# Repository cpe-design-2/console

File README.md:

# `goco`

An open-source video game console for games built using the [Godot game engine](https://godotengine.org).

## Building the console

### Hardware

Flash a microSD card with a fresh image of the Raspberry Pi OS (64-bit) with desktop mode. The targeted device is the Raspberry Pi 3 Model B with 2GB Ram.  

View the [block diagram](./docs/goco-bd.pdf) to understand how the device and its external components combine together to create an open-source console experience.
  
The device's software will be properly initialized using the provided install script.

### Software

The goco consists of the Godot game engine built for the FRT platform and the goco binary executable. The executable is compiled in GitHub Actions for continuous deployment for the necessary target `aarch64-unknown-linux-gnu`. See the [installation script](./install.sh).

## Emulating the console

The console "operating system" application is written in the Rust programming language. It can be tested independent of its targetd Raspberry Pi platform through cross-compilation.

To run the unit tests:
```
cargo test
```

To build the application:
```
cargo build
```

To run the application:
```
cargo run
```

## Environment Variables

The following environment variables affect the console:

- `GOCO_NO_FULLSCREEN`: Disable fullscreen mode during start-up when this environment variable exists

- `GOCO_GODOT_PATH`: The complete path to the Godot engine binary to be invoked when booting a video game from a .pck file.

-  `GOCO_ROOT`: The directory from where to fetch Goco-related files. If this environment variable does not exist then it defaults to using the current working directory '.'.

## Dependencies

At a minimum, the following tools and software are required to get the application built and running:

- The Rust programming language
- Cargo package manager

## User Guide

Supported games are built using Godot version 3.5.1. The games must be specified in .pck format, and an optional icon can be set matching the same file name as the .pck file under the .png image format.

Once the Goco application is running, insert the a USB drive with under the name "GAMESTICK". The dirve is searched on the local host computer and recursively finds all the .pck files to load as the game library.

The game library can be navigated by sending 'A' keys to traverse left, and 'D' keys to traverse right. Sending a 'SPACE' key will enter the currently selected game. Sending 'E' key will eject the currently inserted "GAMESTICK" USB drive.

### Using a RasberryPi System

The Goco application is best suited to be ran on a RaspberryPi computer. An additional circuit is connected to the RaspberryPi's GPIO pins for extended functionality not available on a standard personal computer. See the configuration image [here](./docs/RPI-CIRCUIT.png) for the setup. 

The buttons are configured from left to right as: power button, home button, and eject button. The leftmost LED (green) signals that the system is currently in the POWER state when illuminated. The rightmost LED (yellow) signals that the system detects a USB drive as "GAMESTICK" on the current computer.

The power button has the ability to put the system into a sleep state or power state. When the green LED is illuminated, the system is in POWER state. When the LED is off, the system is in the SLEEP state.

The home button has the ability to send a subprocess command to kill the currently running Godot game engine process. This will return focus to the Goco application if the Godot engine is open. If the Godot engine is not running, there would be no effect.

The eject button has the ability to send a subprocess command to unmount the filesystem drive for the USB drive. When the yellow LED is on, the system detects the USB drive named "GAMESTICK". Pressing the button will remove the drive from the filesystem and set the yellow LED to off.

## Limitations

1. The OpenGL backend is not supported for rendering images on Linux machines for the `iced` crate. This currently prevents properly displaying PNG images for targets that choose to render with the OpenGL backend.
 
Roadblocks encountered:
- failed to compile Vulkan (alternate WGPU_BACKEND) for RaspberryPi OS. See these projects and forums: [rpi-vk-driver/issues](https://github.com/Yours3lf/rpi-vk-driver/issues/6), [vulkan-loader](https://github.com/KhronosGroup/Vulkan-Loader), [vulkan-header](https://github.com/KhronosGroup/Vulkan-Headers/blob/main/BUILD.md).

2. Currently, only the standard version of Godot is supported. The mono version is still under construction in getting a Godot Mono binary compiled for the targeted hardware. See the report for the failed attempts on compiling for Godot Mono [here](./docs/CompilingMonoPi.md)

Roadblocks encountered:
- extremely long compile times for the temporary Godot mono binary

3. Gamepad/Joystick event detection is not supported in the `iced` crate. See the documentation for missing event types: [docs](https://docs.rs/iced/0.8.0/iced/enum.Event.html).

## Lessons and Notes

This project is largely coded in the Rust programming language. Rust is still a fairly new but promising language compared to languages in its domain such as C++. Due to its relative infancy, a lot of crates are still being produced to catch up to the level of C++ library maturity. Rust also has a steep learning curve, which can discourage future development and onboarding developers. However, Rust's build system can be considered very nice to work with as this application used GitHub Actions to automate the process of compiling this application for the Raspberry Pi hardware. It is very easy and encouraging to write unit tests and compile programs across multiple platforms.

With all these points in mind, it is important to look back and evaluate the project's progress and the decisions made along the way. This project, like all others, is an experiment. Experimentation is still encouraged and will always be benefitted from, whether it be in a different language with mature frameworks, or selecting different GUI crates with Rust, or continuing to move forward with the current project's state.

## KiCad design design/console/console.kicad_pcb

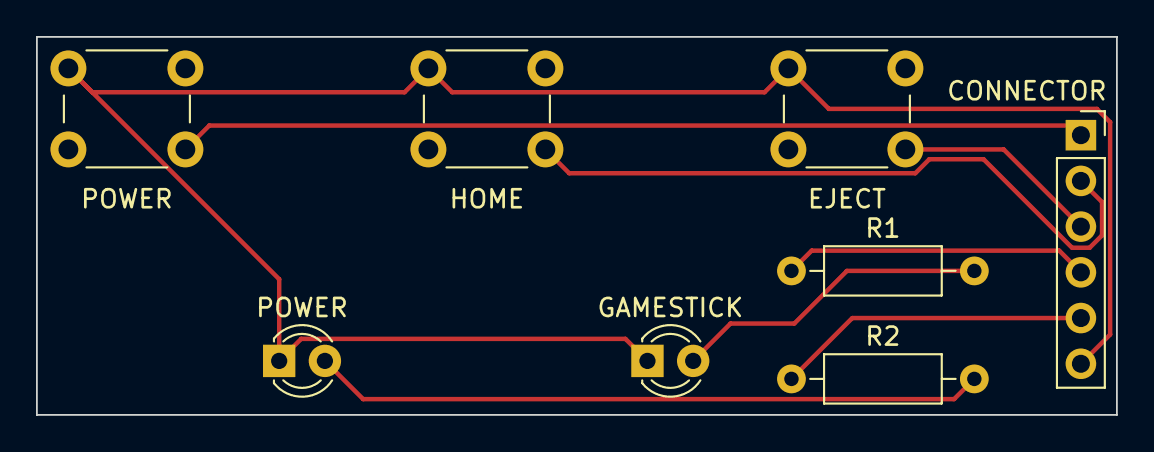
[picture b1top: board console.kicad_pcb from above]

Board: 2 copper layers, 60.0 x 21.0 mm, 8 parts (0 on the bottom side), 8 nets.

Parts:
CONNECTOR: Conn_01x06; PinSocket_1x06_P2.54mm_Vertical
EJECT: 1825910-6; SW_PUSH_4_pin
GAMESTICK: LED; LED_D3.0mm
HOME: 1825910-6; SW_PUSH_4_pin
POWER: EJECT; SW_PUSH_4_pin
POWER#2: LED; LED_D3.0mm
R1, R2: R; R_Axial_DIN0207_L6.3mm_D2.5mm_P10.16mm_Horizontal

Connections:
Earth: CONNECTOR.6, EJECT.1, GAMESTICK.1 (K), HOME.1, POWER.1, POWER#2.1 (K)
unnamed: POWER#2.2 (A), R2.2
unnamed: GAMESTICK.2 (A), R1.2
unnamed: CONNECTOR.1, POWER.4
unnamed: CONNECTOR.2, HOME.4
unnamed: CONNECTOR.3, EJECT.4
unnamed: CONNECTOR.4, R1.1
unnamed: CONNECTOR.5, R2.1

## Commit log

2023-01-24 ci: adds pipeline
2023-01-24 ci: updates build to use rpi3 target
2023-01-24 adds cargo config file
2023-01-24 ci: installs linker
2023-01-24 ci: removes testing for different target
2023-01-24 removes linker step
2023-01-24 ci: removes target configuration
2023-01-24 ci: adds aarch64 compiler
2023-01-24 begins overall installation script
2023-01-24 ci: updates target to musl
2023-01-24 ci: updates linker config
2023-01-24 updates install script
2023-01-25 adds basic gui application used iced dep
2023-01-25 ci: adds necessary compilers
2023-01-25 ci: updates cmake variables
2023-01-25 ci: fixes syntax error
2023-01-25 ci: fixes env var placement
2023-01-25 ci: renames env vars for cmake
2023-01-25 ci: adds aarch64 pkg-config
2023-01-25 ci: rolls back ubuntu image
2023-01-25 ci: adds fontconfig lib
2023-01-25 ci: sets pkg-config path
2023-01-25 ci: adds fontconfig-dev lib
2023-01-25 ci: allows fontconfig to configure dynamically
2023-01-25 ci: adds debugging
2023-01-25 ci: swaps to docker image
2023-01-25 ci: update options for docker
2023-01-25 ci: uses rpi action github
2023-01-25 ci: fixes syntax issues
2023-01-25 ci: adds addtional mb to image
2023-01-25 ci: install rust onto rpi
2023-01-25 ci: swaps to new gh action
2023-01-25 ci: install rust
2023-01-25 ci: installs curl
2023-01-25 ci: sources rust installation for immediate changes:
2023-01-25 ci: installs rust in one-line
2023-01-25 ci: print rustc version
2023-01-25 ci: adds source install
2023-01-25 ci: adds source
2023-01-25 ci: removes apt-pkg source
2023-01-25 ci: moves source to commands
2023-01-25 ci: updates pipeline
2023-01-25 ci: builds rust app
2023-01-25 ci: adds build-essential
2023-01-25 adds iced gui example code
2023-01-25 ci: updates docker image and attempts to use rs-cache
2023-01-25 ci: adds cmake and fontconfig packages
2023-01-25 ci: adds libfontconfig1-dev package
2023-01-26 adds full screen mode to demo app
2023-01-27 docs: updates readme and adds block diagram
2023-01-27 adds license
2023-01-27 polishes readme
2023-01-27 updates readme
2023-01-27 ConsoleDrawing
2023-01-27 Console Working Images
2023-02-05 begins implementing backend gamestick and game library
2023-02-05 updates gamestick library functionality and adds test cases
2023-02-08 adds test for is_game_file
2023-02-08 formats code
2023-02-10 updates test to check for 3 pck files
2023-02-14 adds conditional compilation for windows os
2023-02-14 gets example game running on goco
2023-02-14 adds bare-bones menu functionality with key support
2023-02-17 adds ability to traverse through game library
2023-02-17 fixes tests and adds more games to test environment
2023-02-17 adds tests, comments, and polishes code
2023-02-18 adds feature of detecting gamestick media
2023-02-18 updates install script with steps to set up goco binary
2023-02-19 fixes bug with rpi target not correctly setting gamestick path
2023-02-19 ci: adds packaging job for final distribution
2023-02-19 reads GOCO_ROOT env var for finding 'empty.png'
2023-02-19 ci: fixes copy command in package job
2023-02-19 ci: fixes env var reading during package job
2023-02-19 allows handling of window closing events in initial state
2023-02-20 updates readme about limitations
2023-03-07 adds cargo build feature to build with RPI GPIO crate
2023-03-07 adds example code for rpi feature
2023-03-07 ci: adds potential fix to failing crates.io update
2023-03-07 adds comments and polishes code
2023-03-07 fixes syntax error for handling gpio error
2023-03-09 adds functionality for RPI GPIO LEDs
2023-03-09 fixes missing field for Os struct in test
2023-03-09 adds default initial struct for Io
2023-03-09 adds debug and partialeq traits to Pin enum
2023-03-09 adds input pins
2023-03-09 adds async interrupt for eject button
2023-03-09 adds callbacks for all input pins
2023-03-09 removes unused example code
2023-03-10 adds extra error checks to engine call
2023-03-10 adds functionality for button inputs to modify OS state for RPI
2023-03-10 adds quit game as feature-specific fn
2023-03-10 fixes command for shutdown button feature
2023-03-25 adds 'e' key to eject on non-rpi systems
2023-03-25 updates readme and adds circuit image
2023-04-01 Adding in Design files
2023-04-03 Adding Some Assets
2023-04-10 updates iced crate to 0.8
2023-04-10 adds initial state animation
2023-04-10 polishes code
2023-04-10 updates fresh system install script for console setup
2023-04-10 updates install script to set-up splash screen
2023-04-10 ci: changes goco app to executable in packaging stage
2023-04-10 refactors animation code
2023-04-10 Adding Assets
2023-04-11 updates insert image
2023-04-11 Updated Animation
2023-04-11 ci: updates packaging
2023-04-11 removes old boot video
2023-04-11 organizes assets folder
2023-04-11 adds doc about compiling for Godot Mono
2023-04-11 fixes width alignment for loaded game library
2023-04-11 allows godot instance checking for modern computer targets
2023-04-11 updates compiling mono for future work
2023-04-12 updates version number
2023-04-12 updates readme with notes

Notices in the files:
README.md:
License: MIT
